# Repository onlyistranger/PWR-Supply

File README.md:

PWR-Supply
==========

网上看到的一个可调电源设计稿。

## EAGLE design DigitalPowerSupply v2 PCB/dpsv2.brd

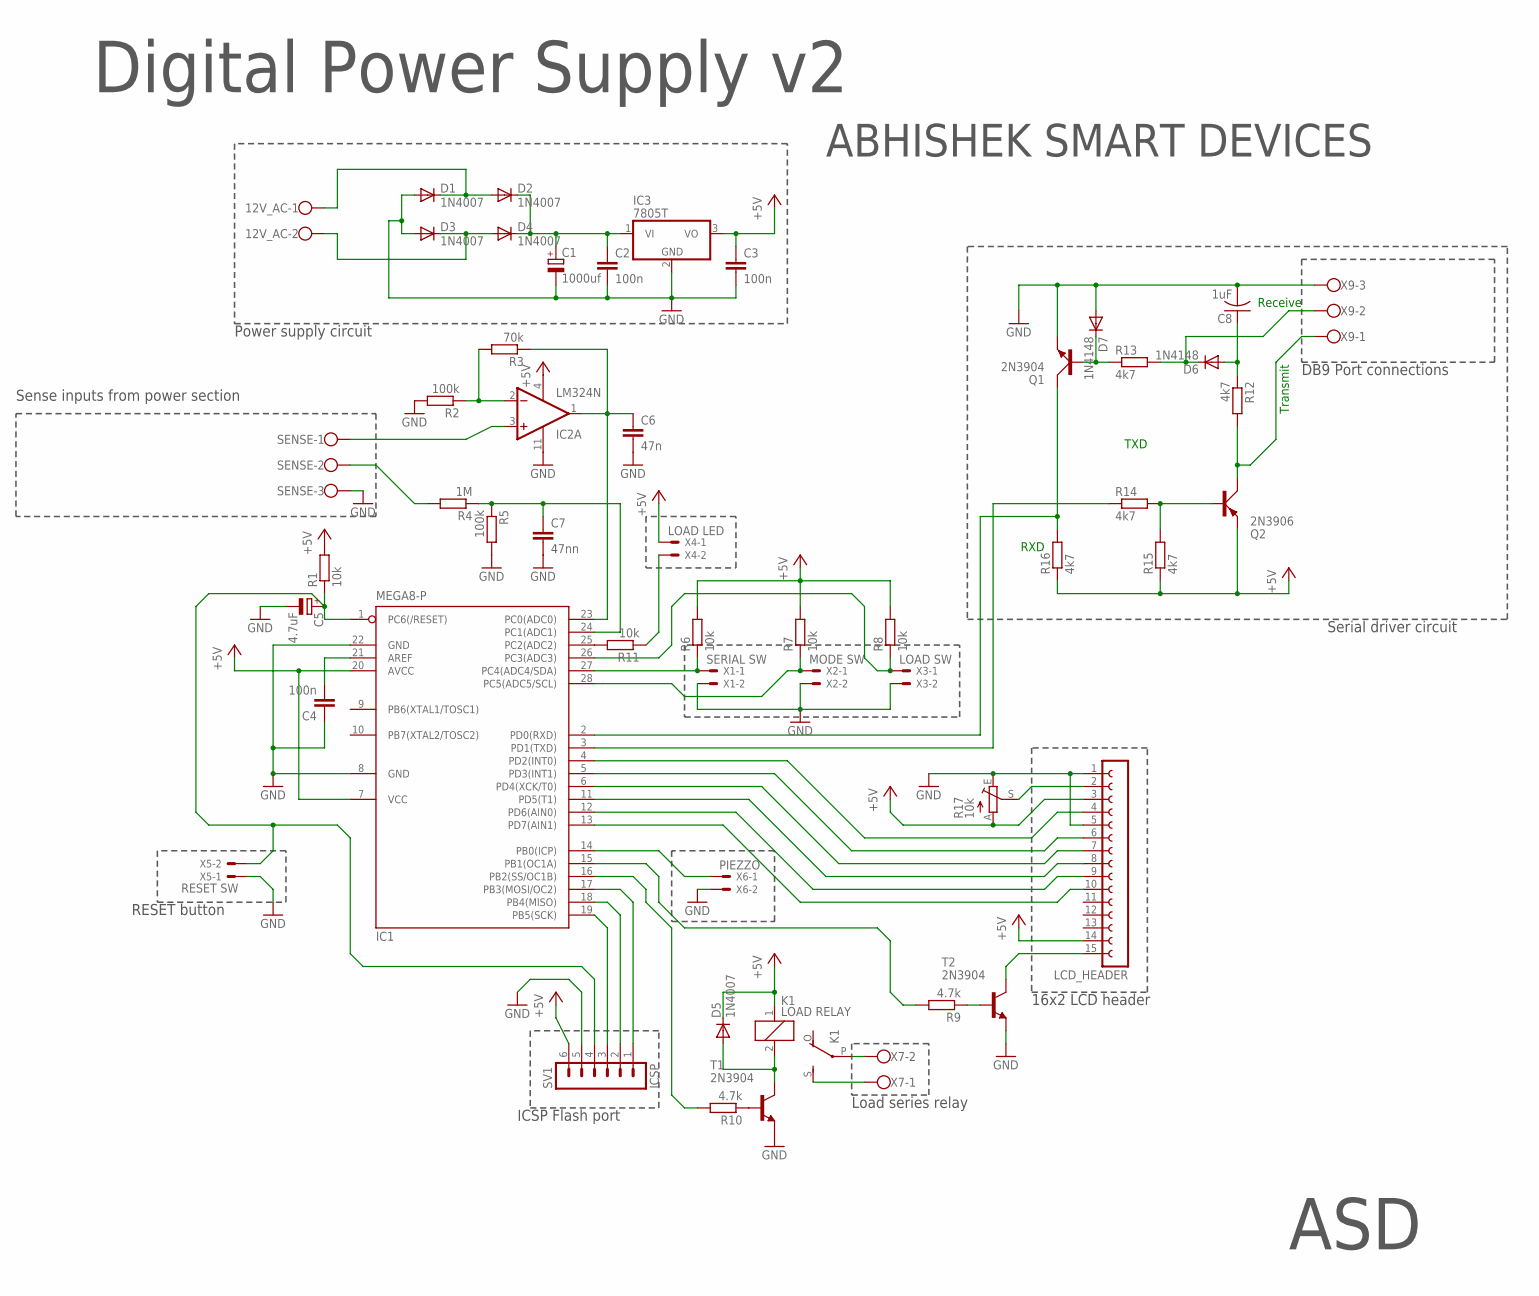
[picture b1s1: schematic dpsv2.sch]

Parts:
12V_AC: W237-102
C1: 1000uf; E5-13
C2, C3, C4: 100n; C102-054X133
C5: 4.7uF; E2,5-7
C6: 47n; C050-025X075
C7: 47nn; C050-025X075
C8: 1uF; C025-040X050
D1, D2, D3, D4, D5: 1N4007; DO07
D6, D7: 1N4148; DO35-10
IC1: MEGA8-P; DIL28-3
IC2: LM324N; DIL14
IC3: 7805T; TO220H
K1: LOAD RELAY; G5LE
LCD_HEADER: FE15-1; FE15
Q1: 2N3904; TO92D
Q2: 2N3906; TO92D
R1, R6, R7, R8, R11: 10k; 0309/12
R2, R5: 100k; 0309/12
R3: 70k; 0309/12
R4: 1M; 0309/12
R9, R10: 4.7k; 0309/12
R12, R13, R14, R15, R16: 4k7; 0309/12
R17: 10k; B25X
SENSE: W237-103
SV1: ICSP; MA06-1
T1, T2: 2N3904; TO92-CBE
X1: SERIAL SW; 22-23-2021
X2: MODE SW; 22-23-2021
X3: LOAD SW; 22-23-2021
X4: LOAD LED; 22-23-2021
X5: RESET SW; 22-23-2021
X6: PIEZZO; 22-23-2021
X7: W237-102
X9: W237-103

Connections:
+5V: C3.1, D5.C, IC1.7 (VCC), IC1.20 (AVCC), IC2.4 (V+), IC3.3 (VO), K1.1, LCD_HEADER.3, LCD_HEADER.14, Q2.E, R1.2, R6.2, R7.2, R8.2, R15.1, R16.1, R17.A, SV1.6, X4.1
GND: C1.-, C2.2, C3.2, C4.1, C5.-, C6.2, C7.2, C8.2, D1.A, D3.A, D7.A, IC1.8 (GND), IC1.22 (GND), IC2.11 (V-), IC3.2 (GND), LCD_HEADER.1, LCD_HEADER.5, Q1.E, R2.2, R5.2, R17.E, SENSE.3, SV1.5, T1.E, T2.E, X1.2, X2.2, X3.2, X5.1, X6.2, X9.3
unnamed: C6.1, IC1.23 (PC0(ADC0)), IC2.1 (OUT), R3.1
unnamed: 12V_AC.1, D1.C, D2.A
unnamed: 12V_AC.2, D3.C, D4.A
unnamed: C1.+, C2.1, D2.C, D4.C, IC3.1 (VI)
unnamed: IC2.3 (+IN), SENSE.1
unnamed: R4.2, SENSE.2
unnamed: C4.2, IC1.21 (AREF)
unnamed: C7.1, IC1.24 (PC1(ADC1)), R4.1, R5.1
unnamed: C5.+, IC1.1 (PC6(/RESET)), R1.1, SV1.4, X5.2
unnamed: IC2.2 (-IN), R2.1, R3.2
unnamed: IC1.27 (PC4(ADC4/SDA)), R6.1, X1.1
unnamed: IC1.28 (PC5(ADC5/SCL)), R7.1, X2.1
unnamed: IC1.26 (PC3(ADC3)), R8.1, X3.1
unnamed: LCD_HEADER.15, T2.C
unnamed: IC1.15 (PB1(OC1A)), R9.2
unnamed: IC1.16 (PB2(SS/OC1B)), R10.2
unnamed: R9.1, T2.B
unnamed: R10.1, T1.B
unnamed: D5.A, K1.2, T1.C
unnamed: IC1.14 (PB0(ICP)), X6.1
unnamed: K1.P, X7.2
unnamed: IC1.25 (PC2(ADC2)), R11.2
unnamed: R11.1, X4.2
unnamed: K1.S, X7.1
unnamed: IC1.17 (PB3(MOSI/OC2)), SV1.1
unnamed: IC1.18 (PB4(MISO)), SV1.2
unnamed: IC1.19 (PB5(SCK)), SV1.3
unnamed: IC1.2 (PD0(RXD)), Q1.C, R16.2
unnamed: Q2.B, R14.2, R15.2
unnamed: C8.1, D6.A, R12.1
unnamed: Q2.C, R12.2, X9.1
unnamed: D7.C, Q1.B, R13.1
unnamed: D6.C, R13.2, X9.2
unnamed: IC1.5 (PD3(INT1)), LCD_HEADER.6
unnamed: IC1.3 (PD1(TXD)), R14.1
unnamed: LCD_HEADER.2, R17.S
unnamed: IC1.6 (PD4(XCK/T0)), LCD_HEADER.7
unnamed: IC1.11 (PD5(T1)), LCD_HEADER.8
unnamed: IC1.12 (PD6(AIN0)), LCD_HEADER.9
unnamed: IC1.4 (PD2(INT0)), LCD_HEADER.4
unnamed: IC1.13 (PD7(AIN1)), LCD_HEADER.10

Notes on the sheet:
TXD
RXD
Transmit
Receive
Digital Power Supply v2
ASD
ABHISHEK SMART DEVICES
ICSP Flash port
RESET button
Sense inputs from power section
Power supply circuit
Serial driver circuit
DB9 Port connections
16x2 LCD header
Load series relay

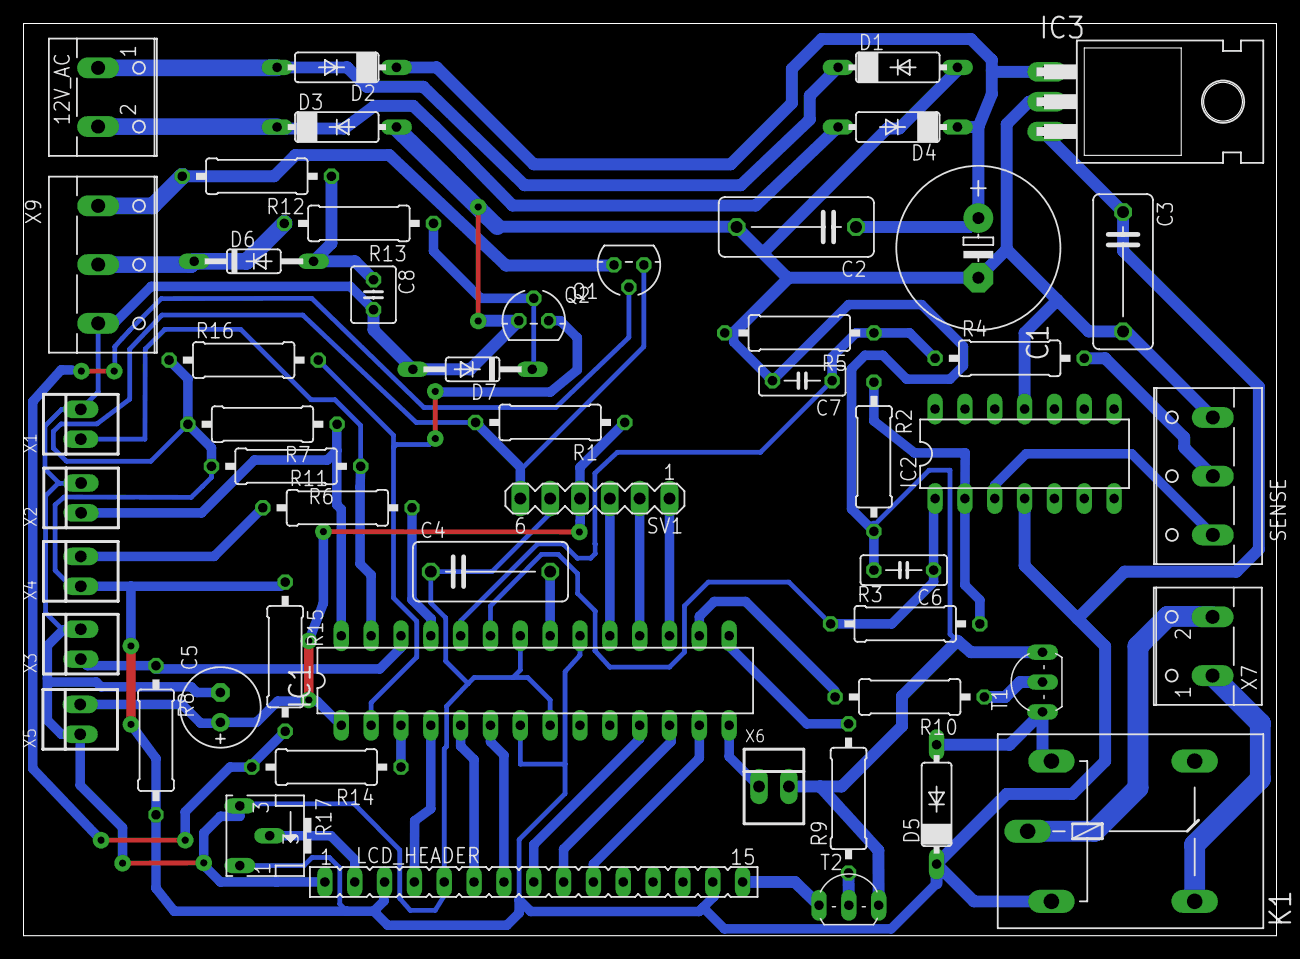
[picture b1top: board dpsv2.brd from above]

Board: 2 copper layers, 106.7 x 77.6 mm, 52 parts (0 on the bottom side), 43 nets.

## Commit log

2013-12-09 原始文件。
